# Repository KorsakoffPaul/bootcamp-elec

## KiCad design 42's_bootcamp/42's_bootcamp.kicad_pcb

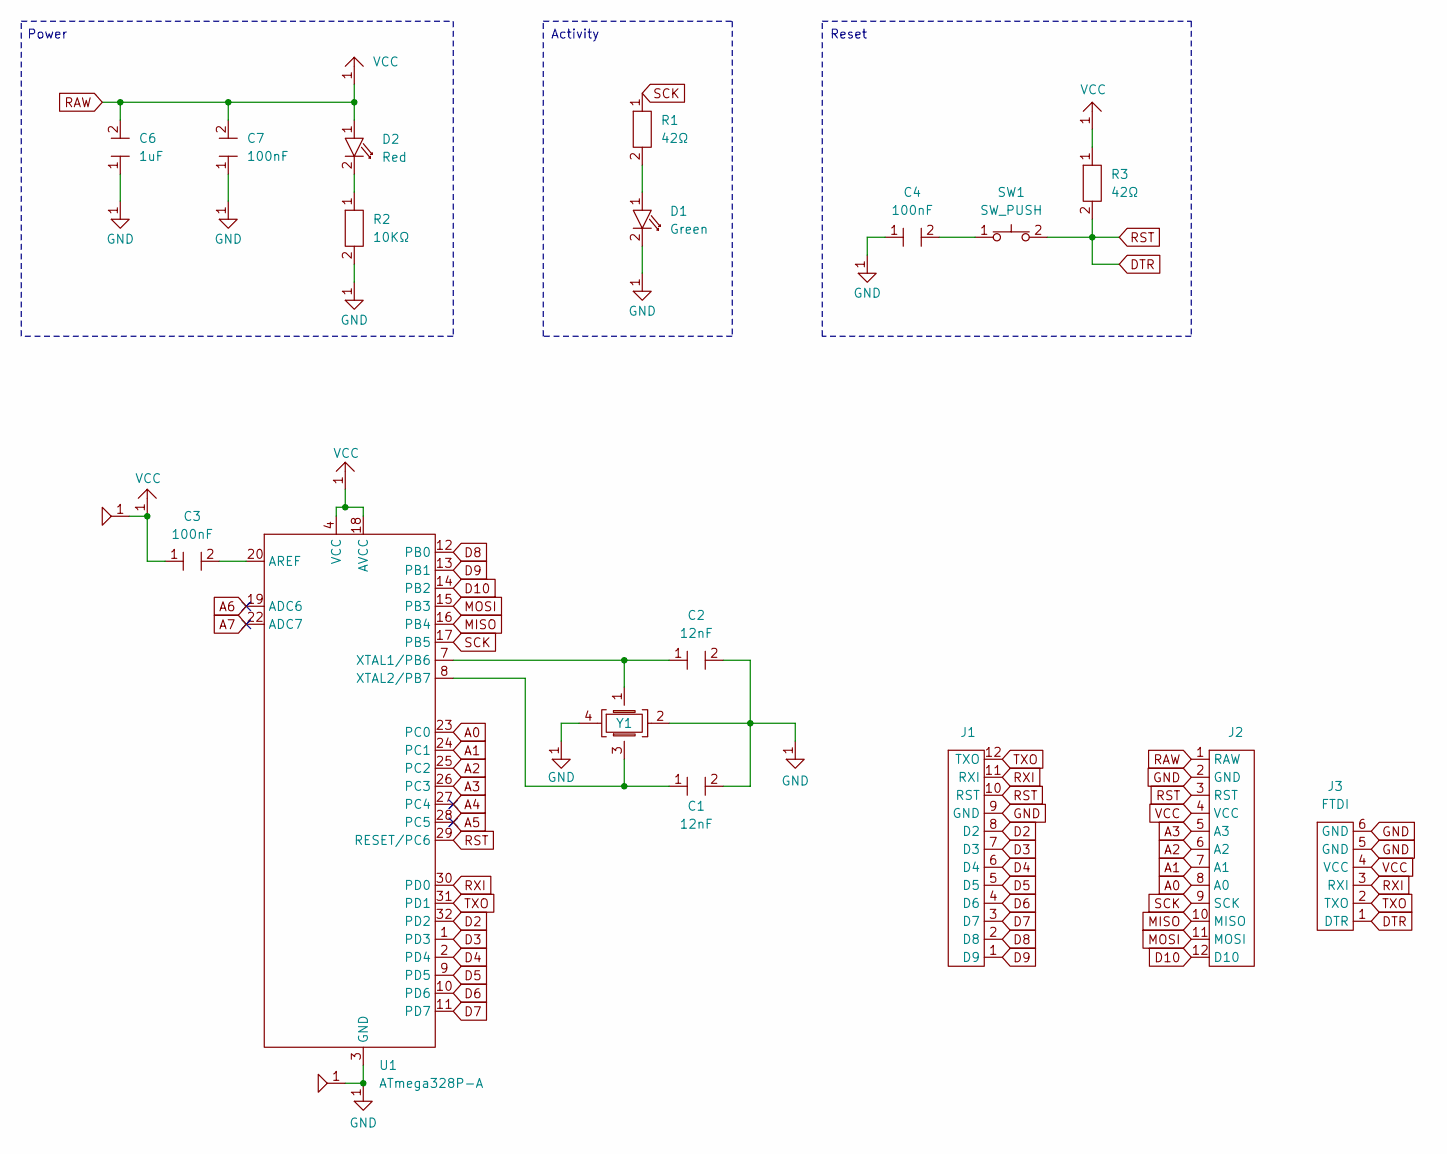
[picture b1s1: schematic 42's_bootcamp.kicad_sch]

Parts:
C1, C2: 12nF; C_0603
C3, C4, C7: 100nF; C_0603
C6: 1uF; C_0603
D1: Green; Led_0603
D2: Red; Led_0603
J1, J2: PinHeader_1x12_P2.54mm
J3: FTDI; PinHeader_1x06_P2.54mm
R1, R3: 42Ω; R_0603
R2: 10KΩ; R_0603
SW1: SW_PUSH; SW_SPST_B3U-1000P
U1: ATmega328P-A; TQFP-32_7x7_Pitch0.8mm
Y1: Crystal_SMD_3225

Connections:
A0: J2.8 (A0), U1.23 (PC0)
A1: J2.7 (A1), U1.24 (PC1)
A2: J2.6 (A2), U1.25 (PC2)
A3: J2.5 (A3), U1.26 (PC3)
A4: U1.27 (PC4)
A5: U1.28 (PC5)
A6: U1.19 (ADC6)
A7: U1.22 (ADC7)
D2: J1.8 (D2), U1.32 (PD2)
D3: J1.7 (D3), U1.1 (PD3)
D4: J1.6 (D4), U1.2 (PD4)
D5: J1.5 (D5), U1.9 (PD5)
D6: J1.4 (D6), U1.10 (PD6)
D7: J1.3 (D7), U1.11 (PD7)
D8: J1.2 (D8), U1.12 (PB0)
D9: J1.1 (D9), U1.13 (PB1)
D10: J2.12 (D10), U1.14 (PB2)
DTR: J1.10 (RST), J2.3 (RST), J3.1 (DTR), R3.2, SW1.2, U1.29 (RESET/PC6)
MISO: J2.10 (MISO), U1.16 (PB4)
MOSI: J2.11 (MOSI), U1.15 (PB3)
unnamed: C4.2, SW1.1
unnamed: D1.1, R1.2
unnamed: D2.2, R2.1
unnamed: C3.2, U1.20 (AREF)
unnamed: C2.1, U1.7 (XTAL1/PB6), Y1.1
unnamed: C1.1, U1.8 (XTAL2/PB7), Y1.3
RXI: J1.11 (RXI), J3.3 (RXI), U1.30 (PD0)
SCK: J2.9 (SCK), R1.1, U1.17 (PB5)
TXO: J1.12 (TXO), J3.2 (TXO), U1.31 (PD1)

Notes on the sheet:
Reset
Activity
Power

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
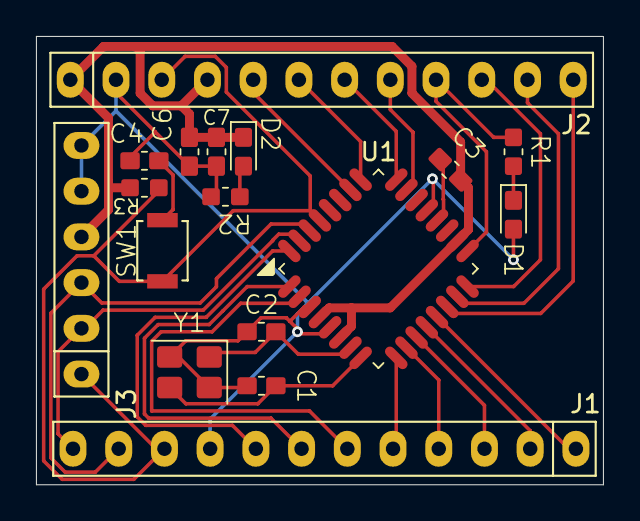
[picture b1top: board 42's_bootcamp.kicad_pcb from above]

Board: 2 copper layers, 31.5 x 24.9 mm, 17 parts (0 on the bottom side), 27 nets.

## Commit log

2026-05-12 creating symbole
2026-05-13 ex1 and 2 done
2026-05-14 footprint, doing pin header
2026-05-15 starting pcb's placement
2026-05-15 time connected
2026-05-16 finished
